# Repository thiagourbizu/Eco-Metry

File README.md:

Bienvenidos a Eco-Metry.
En este repositorio vamos a desarrollar una app en Flutter con Dart, y aparte subimos toda la info que tengamos para organizarnos mejor.
Cualquier foto o imagen que sirva para el proyecto se guarda en la carpeta PDF's

-Matias Galliano
-Thiago Urbizu

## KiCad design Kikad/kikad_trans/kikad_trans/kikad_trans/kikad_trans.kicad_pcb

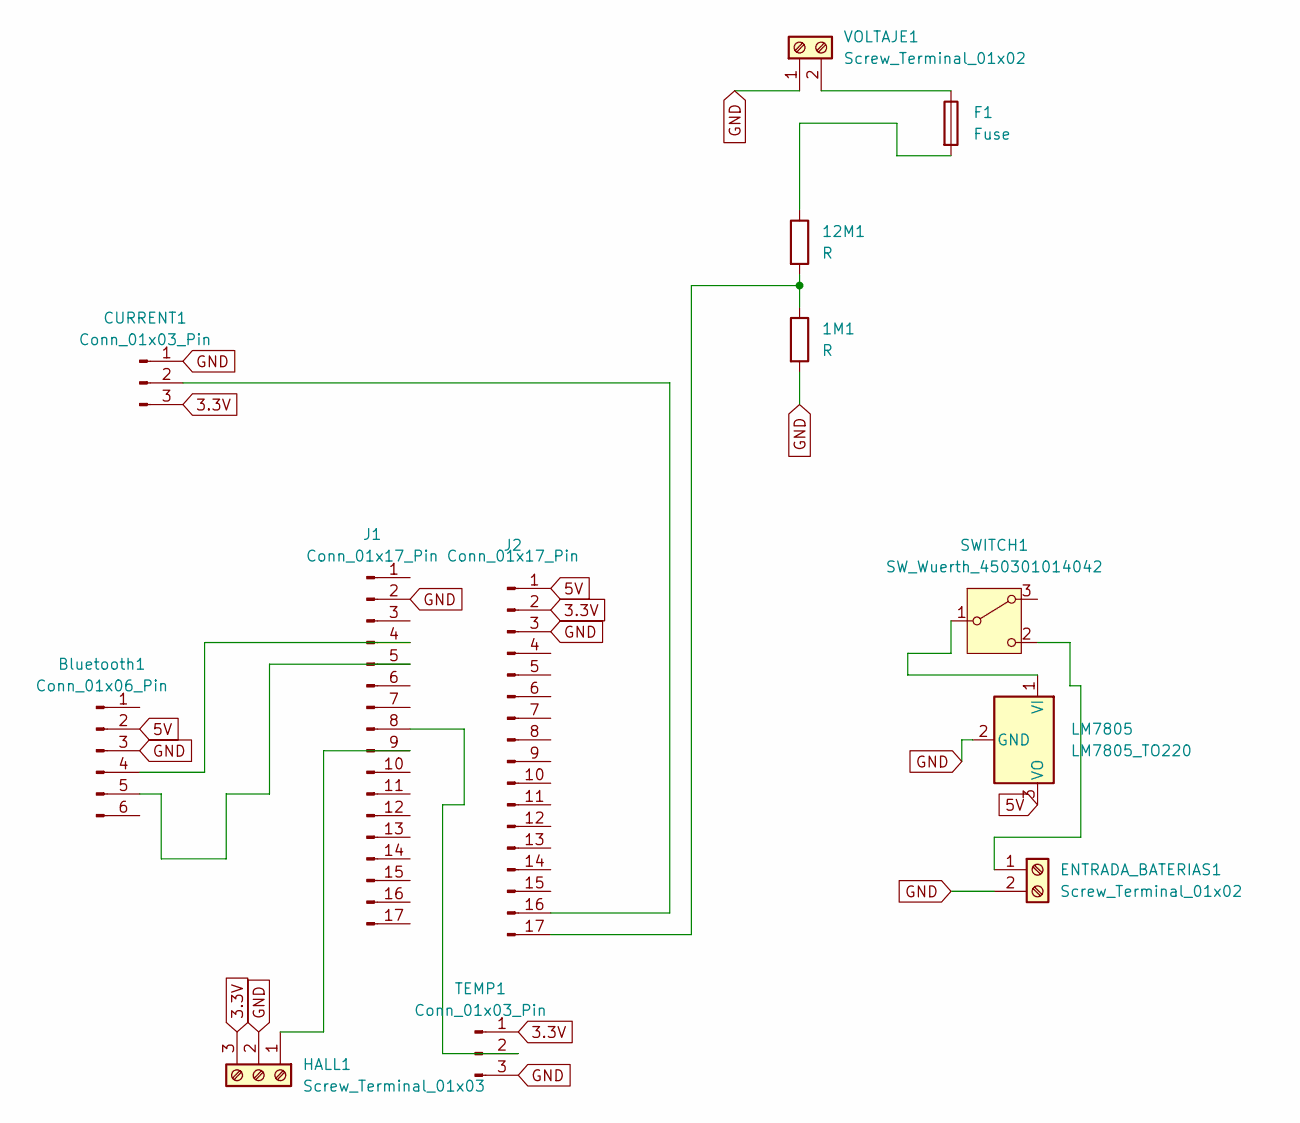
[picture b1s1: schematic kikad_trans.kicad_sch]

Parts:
1M1, 12M1: R; R_Axial_DIN0207_L6.3mm_D2.5mm_P7.62mm_Horizontal
Bluetooth1: Conn_01x06_Pin; PinSocket_1x06_P2.54mm_Vertical
CURRENT1: Conn_01x03_Pin; PinSocket_1x03_P2.54mm_Vertical
ENTRADA_BATERIAS1: Screw_Terminal_01x02; TerminalBlock_Altech_AK300-2_P5.00mm
F1: Fuse; Fuse_Bourns_MF-RG650
HALL1: Screw_Terminal_01x03; TerminalBlock_Altech_AK300-3_P5.00mm
J1, J2: Conn_01x17_Pin; PinSocket_1x17_P2.54mm_Vertical
LM7805: LM7805_TO220; TO-220-3_Vertical
SWITCH1: SW_Wuerth_450301014042; SW_Slide-03_Wuerth-WS-SLTV_10x2.5x6.4_P2.54mm
TEMP1: Conn_01x03_Pin; PinSocket_1x03_P2.54mm_Vertical
VOLTAJE1: Screw_Terminal_01x02; TerminalBlock_Altech_AK300-2_P5.00mm

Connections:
3.3V: CURRENT1.3, HALL1.3, J2.2, TEMP1.1
5V: Bluetooth1.2, J2.1, LM7805.3 (VO)
GND: 1M1.2, Bluetooth1.3, CURRENT1.1, ENTRADA_BATERIAS1.2, HALL1.2, J1.2, J2.3, LM7805.2 (GND), TEMP1.3, VOLTAJE1.1
unnamed: 12M1.1, F1.2
unnamed: Bluetooth1.4, J1.4
unnamed: Bluetooth1.5, J1.5
unnamed: CURRENT1.2, J2.16
unnamed: ENTRADA_BATERIAS1.1, SWITCH1.2 (C)
unnamed: HALL1.1, J1.9
unnamed: J1.8, TEMP1.2
unnamed: 1M1.1, 12M1.2, J2.17
unnamed: LM7805.1 (VI), SWITCH1.1 (B)
unnamed: F1.1, VOLTAJE1.2

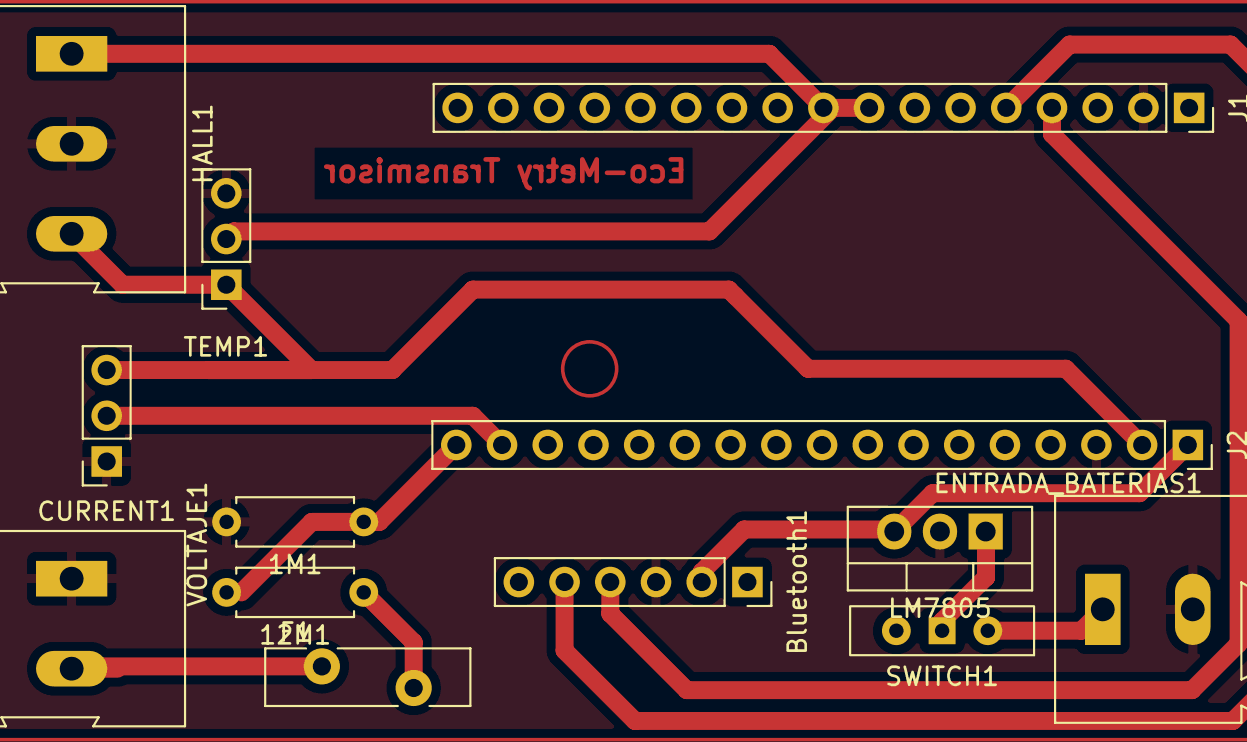
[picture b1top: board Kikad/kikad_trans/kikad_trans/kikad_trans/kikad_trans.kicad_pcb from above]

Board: 2 copper layers, 13 parts (0 on the bottom side), 13 nets.

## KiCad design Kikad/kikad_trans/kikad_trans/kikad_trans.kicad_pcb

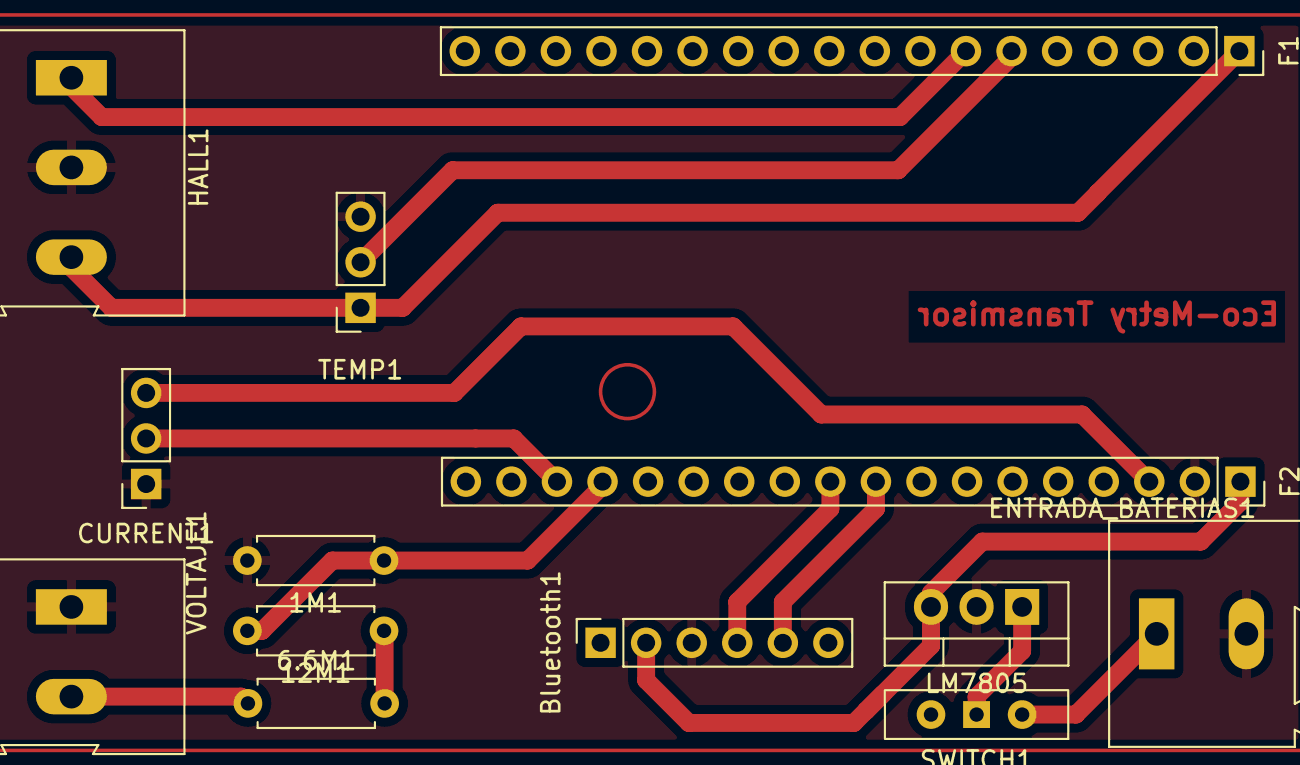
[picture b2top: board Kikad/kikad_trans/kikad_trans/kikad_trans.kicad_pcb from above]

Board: 2 copper layers, 13 parts (0 on the bottom side), 14 nets.

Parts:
1M1, 6.6M1, 12M1: R; R_Axial_DIN0207_L6.3mm_D2.5mm_P7.62mm_Horizontal
Bluetooth1: Conn_01x06_Pin; PinSocket_1x06_P2.54mm_Vertical
CURRENT1: Conn_01x03_Pin; PinSocket_1x03_P2.54mm_Vertical
ENTRADA_BATERIAS1: Screw_Terminal_01x02; TerminalBlock_Altech_AK300-2_P5.00mm
F1, F2: Conn_01x18_Pin; PinSocket_1x18_P2.54mm_Vertical
HALL1: Screw_Terminal_01x03; TerminalBlock_Altech_AK300-3_P5.00mm
LM7805: LM7805_TO220; TO-220-3_Vertical
SWITCH1: SW_Wuerth_450301014042; SW_Slide-03_Wuerth-WS-SLTV_10x2.5x6.4_P2.54mm
TEMP1: Conn_01x03_Pin; PinSocket_1x03_P2.54mm_Vertical
VOLTAJE1: Screw_Terminal_01x02; TerminalBlock_Altech_AK300-2_P5.00mm

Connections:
3.3V: CURRENT1.3, F2.3
5V: Bluetooth1.2, F2.1, LM7805.3 (VO)
GND: 1M1.2, Bluetooth1.3, CURRENT1.1, ENTRADA_BATERIAS1.2, F2.2, HALL1.2, LM7805.2 (GND), TEMP1.3, VOLTAJE1.1
unnamed: 6.6M1.2, 12M1.1
unnamed: Bluetooth1.4, F2.10
unnamed: Bluetooth1.5, F2.9
unnamed: CURRENT1.2, F2.16
unnamed: ENTRADA_BATERIAS1.1, SWITCH1.2 (C)
unnamed: F1.1, HALL1.3, TEMP1.1
unnamed: F1.6, TEMP1.2
unnamed: F1.7, HALL1.1
unnamed: 1M1.1, 12M1.2, F2.15
unnamed: LM7805.1 (VI), SWITCH1.1 (B)
unnamed: 6.6M1.1, VOLTAJE1.2

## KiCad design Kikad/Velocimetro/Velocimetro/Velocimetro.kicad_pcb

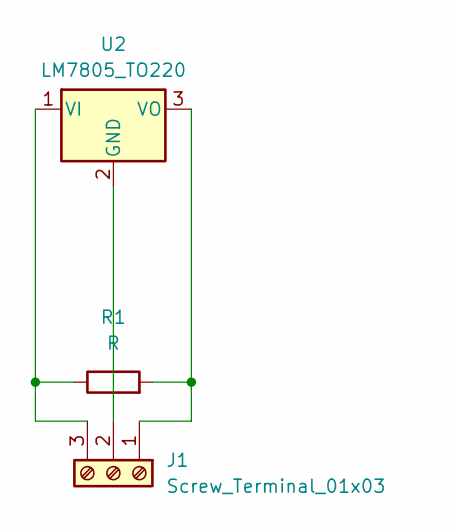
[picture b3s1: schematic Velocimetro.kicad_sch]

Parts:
J1: Screw_Terminal_01x03; TerminalBlock_Altech_AK300-3_P5.00mm
R1: R; R_Axial_DIN0204_L3.6mm_D1.6mm_P5.08mm_Horizontal
U2: LM7805_TO220; TO-220-3_Vertical

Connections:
GND: J1.2, U2.2 (GND)
unnamed: J1.1, R1.2, U2.3 (VO)
unnamed: J1.3, R1.1, U2.1 (VI)

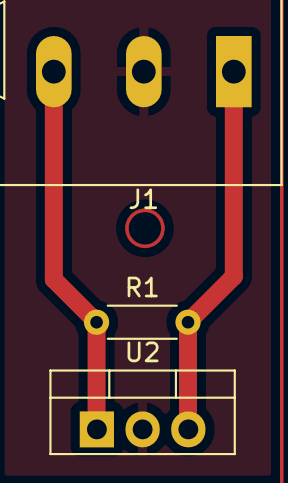
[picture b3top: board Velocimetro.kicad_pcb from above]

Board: 2 copper layers, 3 parts (0 on the bottom side), 3 nets.

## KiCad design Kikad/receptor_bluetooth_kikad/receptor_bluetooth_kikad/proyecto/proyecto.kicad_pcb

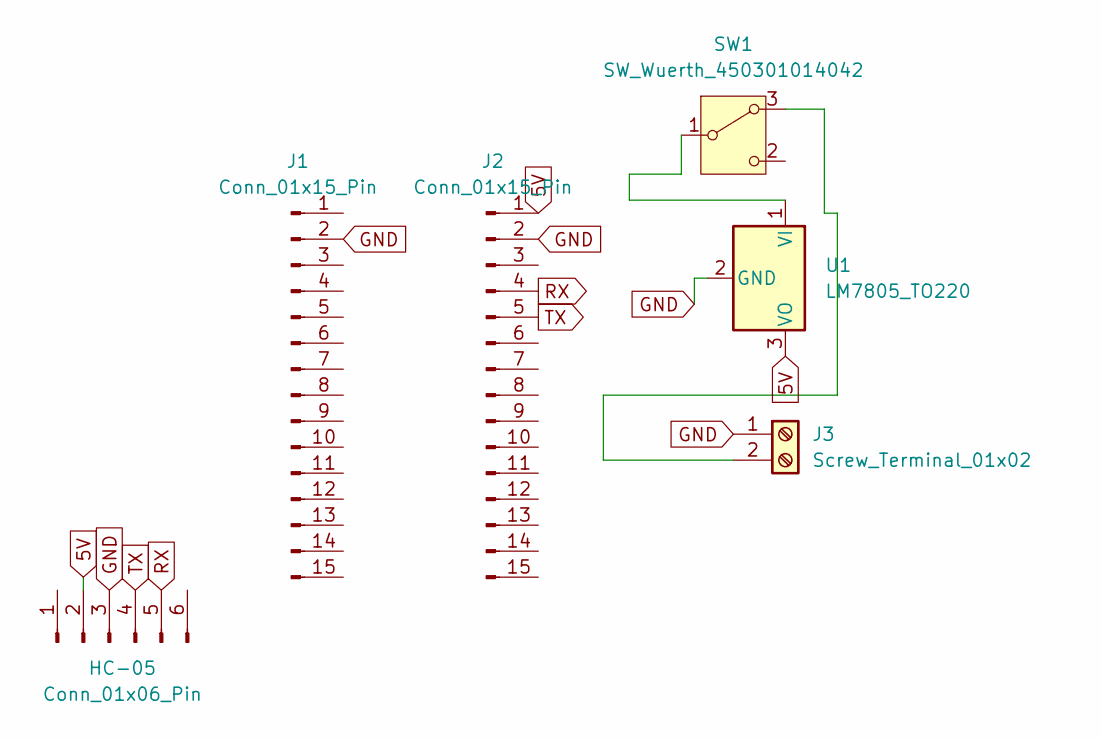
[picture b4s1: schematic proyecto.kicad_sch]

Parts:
HC-05: Conn_01x06_Pin; PinSocket_1x06_P2.54mm_Vertical
J1, J2: Conn_01x15_Pin; PinSocket_1x15_P2.54mm_Vertical
J3: Screw_Terminal_01x02; TerminalBlock_Altech_AK300-2_P5.00mm
SW1: SW_Wuerth_450301014042; SW_Slide-03_Wuerth-WS-SLTV_10x2.5x6.4_P2.54mm
U1: LM7805_TO220; TO-220-3_Vertical

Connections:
5V: HC-05.2, J2.1, U1.3 (VO)
GND: HC-05.3, J1.2, J2.2, J3.1, U1.2 (GND)
unnamed: J3.2, SW1.3 (A)
unnamed: SW1.1 (B), U1.1 (VI)
RX: HC-05.5, J2.4
TX: HC-05.4, J2.5

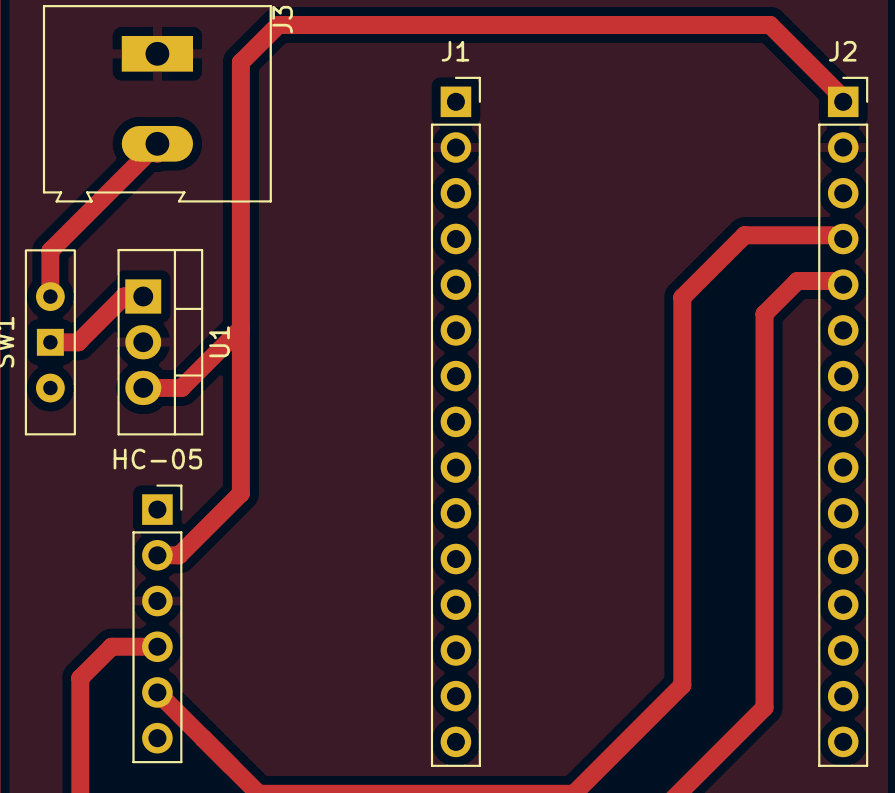
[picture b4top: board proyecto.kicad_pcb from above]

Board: 2 copper layers, 6 parts (0 on the bottom side), 6 nets.

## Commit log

2024-08-05 Volver a empezar
2024-08-05 commitmati
2024-08-06 Color bt
2024-08-06 colorbt
2024-08-06 .ino changes
2024-08-06 kikad
    ....
2024-08-06 btcolor
2024-08-06 KiKAD better
2024-08-06 tempbutton
2024-08-06 prueba 30 datos, boton temp
2024-08-06 velocidadbutton
2024-08-06 hola
2024-08-06 colorgrafico
2024-08-06 colorgrafico2
2024-08-06 graficos
2024-08-06 .ino cambios cadena
2024-08-06 arreglo de graficos
2024-08-06 nombreapp
2024-08-06 cuadrados tension y amperaje
2024-08-07 agregado de voltaje y amperaje !!!!
2024-08-07 milanesa
2024-08-07 mezcla
2024-08-07 primeras pruebas data
2024-08-07 boton duncionando con 50 datos
2024-08-08 agregado de stopper bluetooth y cambios al log
2024-08-08 shunt code
2024-08-08 cambios generales
2024-08-08 mpu code
2024-08-08 receptor kikad
2024-08-08 mpu code speed
2024-08-08 cambios
2024-08-08 pinga
2024-08-10 adruino mpucode
2024-08-12 mpu6050 velocidad working
2024-08-12 bluetooth code
2024-08-12 final
2024-08-12 vvvv
2024-08-13 pantallahorizontal y cambios visuales
2024-08-13 cambio horizontal cuadrado y pruebas boton github
2024-08-13 boton que no anda
2024-08-15 supuesto speedometer (sin probar)
2024-08-19 cambios en .ino
2024-08-19 vamos
2024-08-20 cambios pantalla
2024-08-20 pantalla horizntal con speedometer listo
2024-08-21 test1 reciver bluetooth
2024-08-22 no pude hacerlo la concha de tu madre muerta
2024-08-23 librerias
2024-08-25 velocimetro funcando!!!!
2024-08-25 non important changes
2024-08-25 cambios de colores y boludeces
2024-08-25 cambios boludos...
2024-08-26 pdf final
2024-08-26 code
2024-08-27 agregado de settings!!!
2024-08-28 anduvo la ctd
2024-08-28 kikad update
2024-08-28 github boton
2024-08-28 pdf ahroa si
2024-08-29 ulitmo code funcando!
2024-09-03 agregado de settingsmanager y kikad
2024-09-03 cumulus
2024-09-03 Cumulus v2
2024-09-03 Cumulus v3
2024-09-03 Cumulus desaparece
2024-09-04 mpu andando????? nosesabe
2024-09-05 avances en kikad...
2024-09-26 some changes
2024-10-01 next changes
2024-10-08 kikad vel
2024-10-08 velocimetro finished
2024-10-08 next
2024-10-09 ahora si
2024-10-10 A3114 works
2024-10-10 Kikad Trans Almost Finished
2024-10-10 game test
2024-10-13 cambios en kikad y en codigo completo del sender
2024-10-13 kikad
2024-10-13 Kikad ahora si
2024-10-14 ahora si lcdtm
2024-10-14 cambios de logos y colores app y agregado de rpm y humedad
2024-10-15 ajustes varios(app y .ino)
2024-10-15 el juego mas insano
2024-10-15 speedometer?
2024-10-17 codigo velocimetro chatopenao
2024-10-17 code RPM
2024-10-21 SenderRPM y cambio de la app
2024-10-22 agregado de botones y warnings
2024-10-23 Drawers y Botones insa
2024-11-20 Sin botones insanos
2024-11-22 verga
2024-11-23 EL MEJOR CODIGO EXISTENTE
2024-11-28 Sender stickv2
2024-11-29 porximo GIT con changes importatntye
